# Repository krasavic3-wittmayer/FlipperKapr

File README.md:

# Flipper Kapr 🐟

Flipper Kapr is a **DIY Arduino-based experimental device**, inspired by tools like Flipper Zero.  
Its purpose is **learning, experimentation, and exploration of embedded systems and communication protocols**, not hacking or illegal activity.

This project is mainly educational and was built to understand how different modules and signals work together on microcontrollers.

## What is this?

Flipper Kapr is a personal Arduino project that combines multiple modules into a single device for:

- experimenting with signals and protocols  
- learning how hardware modules communicate  
- understanding embedded programming in practice  

It is **not** a “one-click hack tool” and does **not** magically break secure systems.

## Features

Depending on the build/version, Flipper Kapr may include:

- Infrared (IR) signal sending and receiving  
- NFC / RFID experiments  
- Simple UI (buttons, LEDs, display – if connected)  

Features depend on the hardware you attach.

## Hardware

Typical components used:

### Arduino Mega 2560

- IR transmitter / receiver  
- RFID module (e.g. 13.56 MHz / 125 kHz)  
- **Bad USB** (emulates a keyboard and sends keystrokes when connected to a computer)  

Exact wiring and modules may vary.

## Software

### Arduino (C/C++)

- Uses standard Arduino libraries and module-specific libraries  
- Code is kept simple and readable for learning purposes  

## How to use

1. Connect the hardware modules according to your setup  
2. Open the project in the Arduino IDE  
3. Select the correct board and port  
4. Upload the code  
5. Experiment responsibly  

## Legal & Ethical Notice

Flipper Kapr is intended **only for educational and experimental use**.  
You are responsible for how you use this project and any connected hardware.  
Do not use it to interfere with systems you do not own or have permission to test.

## License

This project is licensed under the **MIT License**.  
You are free to use, modify, and share it, **without any warranty**.

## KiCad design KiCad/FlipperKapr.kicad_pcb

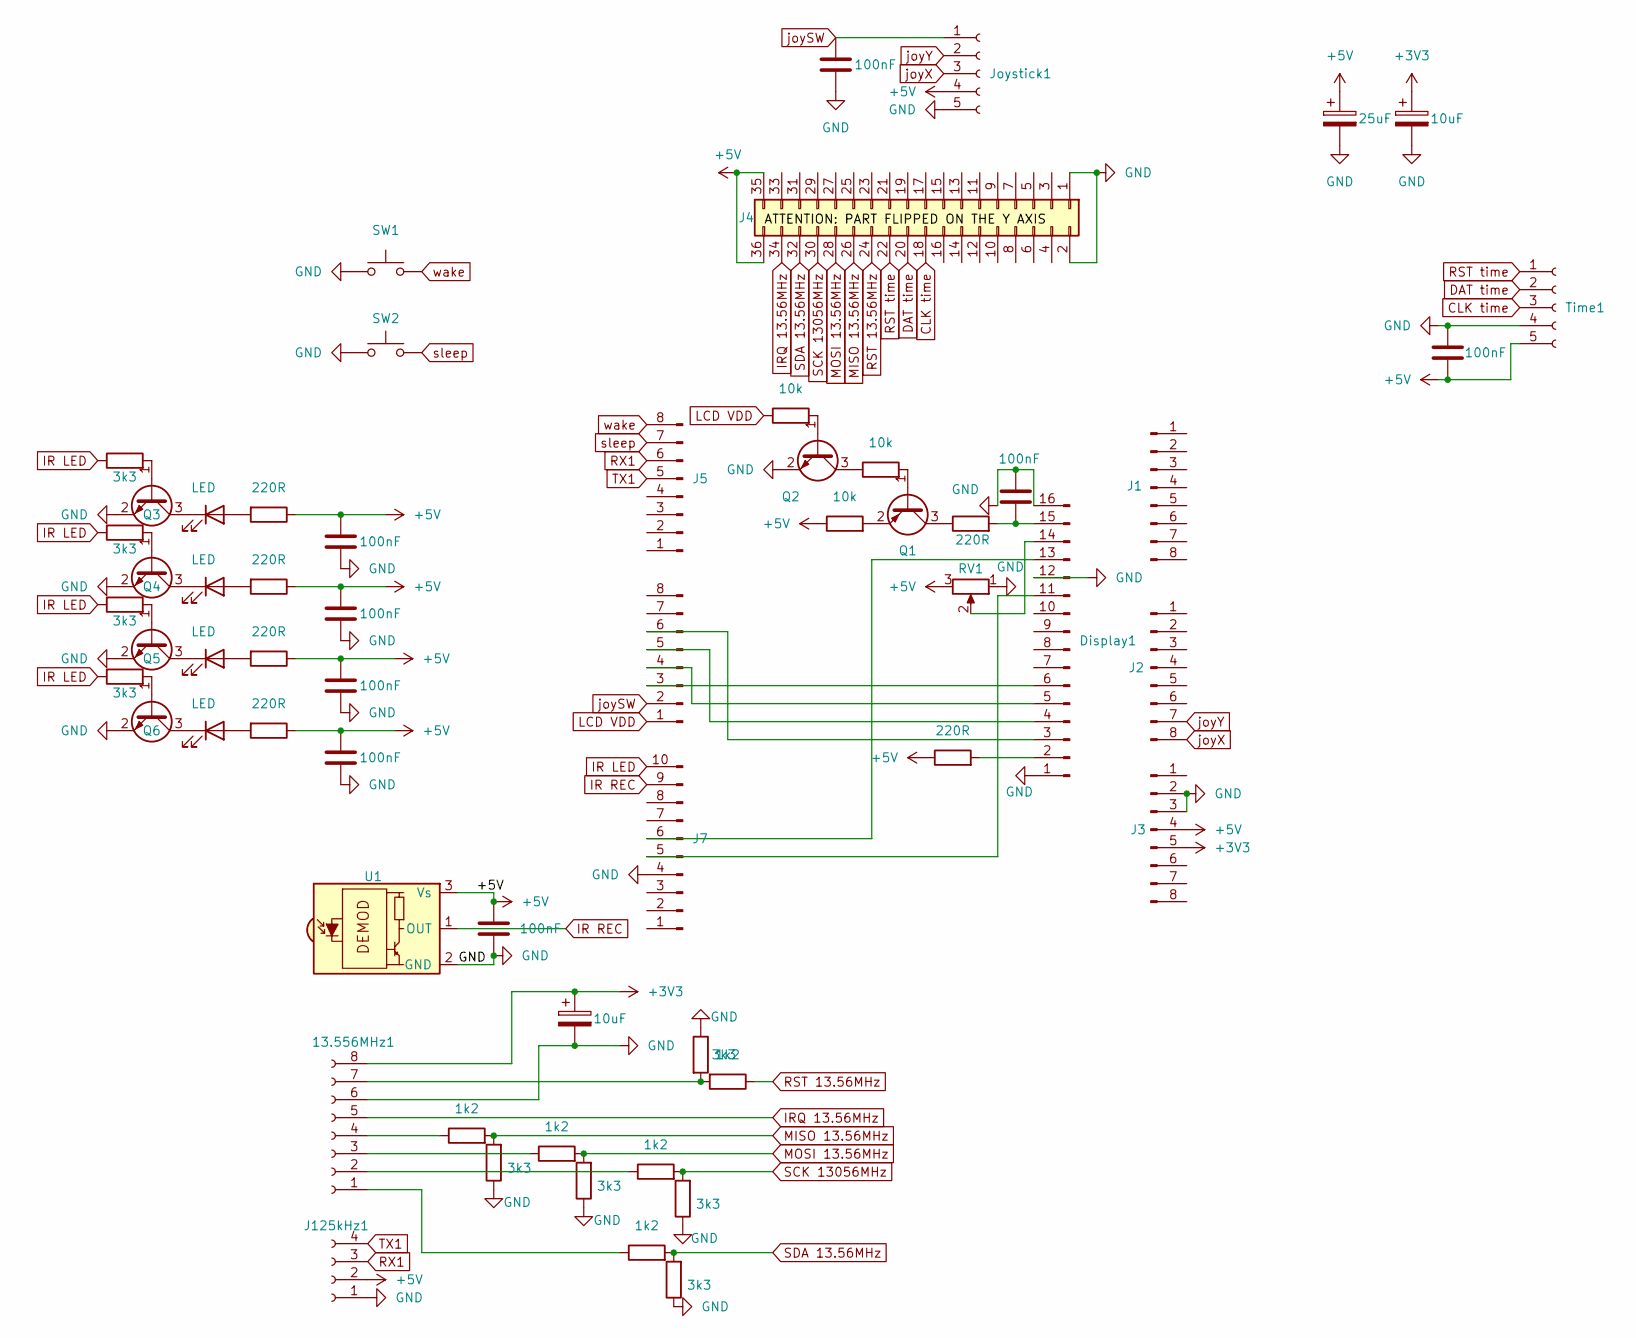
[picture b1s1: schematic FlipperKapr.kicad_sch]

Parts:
13.556MHz1: Conn_01x08_Socket; PinSocket_1x08_P2.54mm_Vertical
C1, C2, C5, C7, C8, C9, C10, C11: 100nF; C_0805_2012Metric
C3: 25uF; C_1206_3216Metric
C4, C6: 10uF; C_1206_3216Metric
D1, D2, D3, D4: LED; LED_1206_3216Metric
Display1: Conn_01x16_Pin; PinSocket_1x18_P2.54mm_Vertical
J1, J2, J3, J5, J6: Conn_01x08_Pin; PinHeader_1x08_P2.54mm_Vertical
J4: Conn_02x18_Odd_Even; PinHeader_2x18_P2.54mm_Vertical
J7: Conn_01x10_Pin; PinHeader_1x10_P2.54mm_Vertical
J125kHz1: Conn_01x04_Socket; PinSocket_1x04_P2.54mm_Vertical
Joystick1: Conn_01x05_Socket; PinSocket_1x05_P2.54mm_Vertical
Q1: SS8550; SOT-23
Q2, Q3, Q4, Q5, Q6: SS8050; SOT-23
R1, R4: 220R; R_0805_2012Metric
R2, R3, R5: 10k; R_0805_2012Metric
R6, R7, R8, R9: 220R; R_1206_3216Metric
R10, R11, R12, R13, R15, R17, R19, R21, R23: 3k3; R_0805_2012Metric
R14, R16, R18, R20, R22: 1k2; R_0805_2012Metric
RV1: R_Potentiometer; Potentiometer_Bourns_3314G_Vertical
SW1, SW2: SW_Push; SW_PUSH-12mm_Wuerth-430476085716
Time1: Conn_01x05_Socket; PinSocket_1x05_P2.54mm_Vertical
U1: TSDP341xx; Vishay_MOLD-3Pin

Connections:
+3V3: 13.556MHz1.8, C4.1, C6.1, J3.5
+5V: C2.1, C3.1, C7.1, C8.1, C9.1, C10.1, C11.2, J3.4, J4.35, J4.36, J125kHz1.2, Joystick1.4, R4.1, R5.1, R6.1, R7.1, R8.1, R9.1, RV1.3, Time1.5, U1.3 (Vs)
CLK time: J4.18, Time1.3
DAT time: J4.20, Time1.2
GND: 13.556MHz1.6, C1.1, C2.2, C3.2, C4.2, C5.2, C6.2, C7.2, C8.2, C9.2, C10.2, C11.1, Display1.1, Display1.12, Display1.16, J3.2, J3.3, J4.1, J4.2, J7.4, J125kHz1.1, Joystick1.5, Q2.2 (E), Q3.2 (E), Q4.2 (E), Q5.2 (E), Q6.2 (E), R15.1, R17.1, R19.1, R21.1, R23.1, RV1.1, SW1.1, SW2.1, Time1.4, U1.2 (GND)
IR LED: J7.10, R10.1, R11.1, R12.1, R13.1
IR REC: J7.9, U1.1 (OUT)
IRQ 13.56MHz: 13.556MHz1.5, J4.34
LCD VDD: J6.1, R3.1
MISO 13.56MHz: J4.26, R20.2, R21.2
MOSI 13.56MHz: J4.28, R18.2, R19.2
unnamed: 13.556MHz1.1, R14.1
unnamed: 13.556MHz1.2, R16.1
unnamed: 13.556MHz1.3, R18.1
unnamed: 13.556MHz1.4, R20.1
unnamed: 13.556MHz1.7, R22.2, R23.2
unnamed: D1.2 (A), R6.2
unnamed: D1.1 (K), Q3.3 (C)
unnamed: D2.2 (A), R7.2
unnamed: D2.1 (K), Q4.3 (C)
unnamed: D3.2 (A), R8.2
unnamed: D3.1 (K), Q5.3 (C)
unnamed: D4.2 (A), R9.2
unnamed: D4.1 (K), Q6.3 (C)
unnamed: Display1.2, R4.2
unnamed: Display1.3, J6.6
unnamed: Display1.4, J6.5
unnamed: Display1.5, J6.4
unnamed: Display1.6, J6.3
unnamed: Display1.11, J7.5
unnamed: Display1.13, J7.6
unnamed: Display1.14, RV1.2
unnamed: C1.2, Display1.15, R1.2
unnamed: Q1.1 (B), R2.2
unnamed: Q1.3 (C), R1.1
unnamed: Q1.2 (E), R5.2
unnamed: Q2.1 (B), R3.2
unnamed: Q2.3 (C), R2.1
unnamed: Q3.1 (B), R10.2
unnamed: Q4.1 (B), R11.2
unnamed: Q5.1 (B), R12.2
unnamed: Q6.1 (B), R13.2
RST 13.56MHz: J4.24, R22.1
RST time: J4.22, Time1.1
RX1: J5.6, J125kHz1.3
SCK 13056MHz: J4.30, R16.2, R17.2
SDA 13.56MHz: J4.32, R14.2, R15.2
TX1: J5.5, J125kHz1.4
joySW: C5.1, J6.2, Joystick1.1
joyX: J2.8, Joystick1.3
joyY: J2.7, Joystick1.2
sleep: J5.7, SW2.2
wake: J5.8, SW1.2

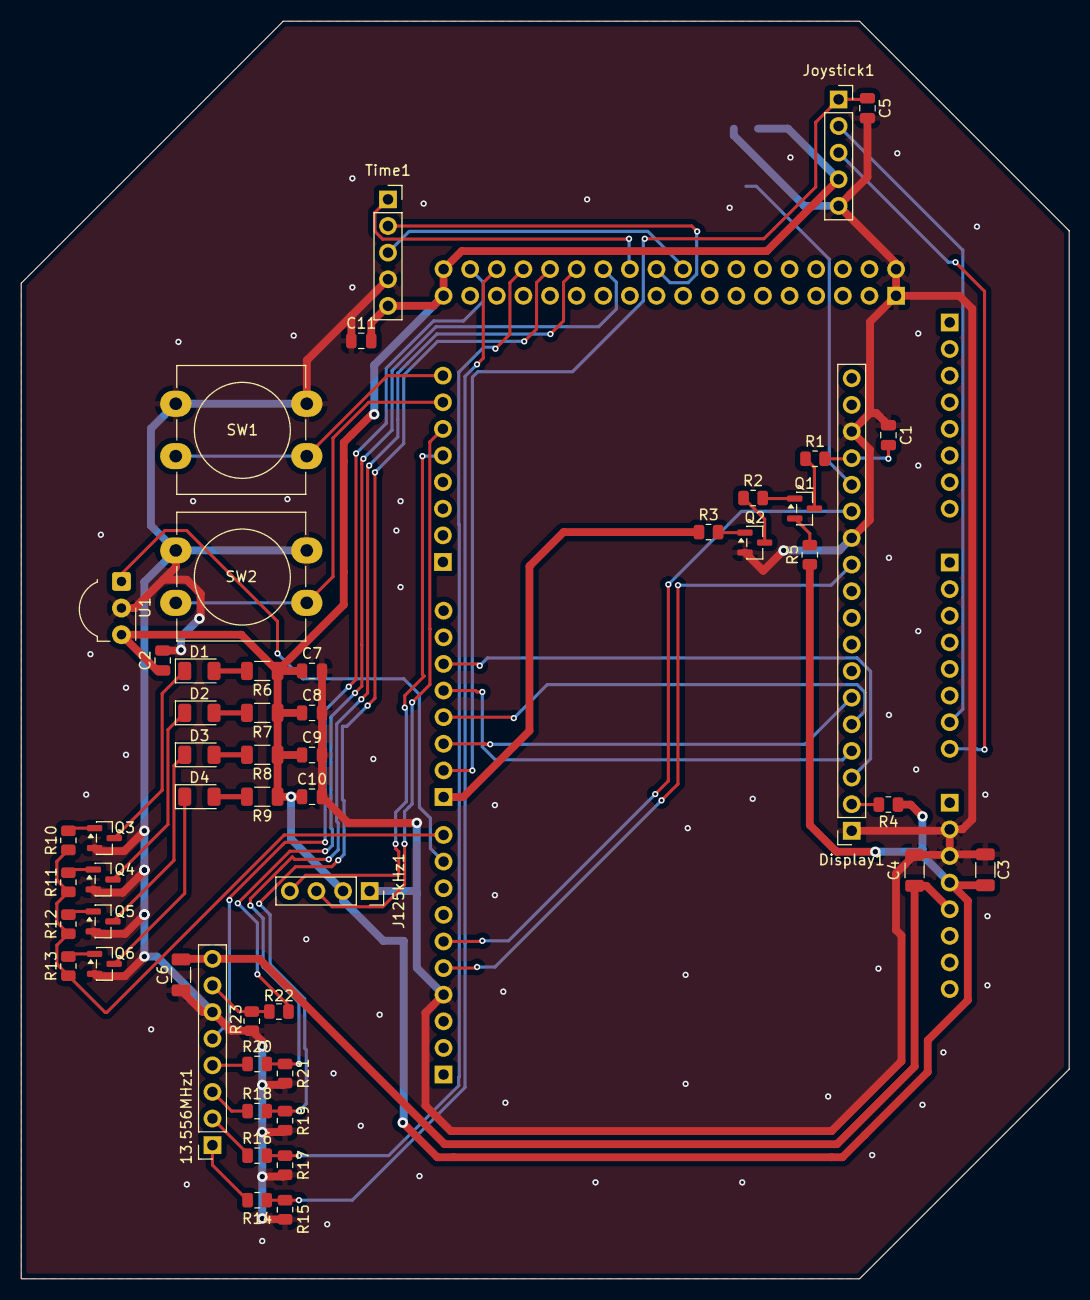
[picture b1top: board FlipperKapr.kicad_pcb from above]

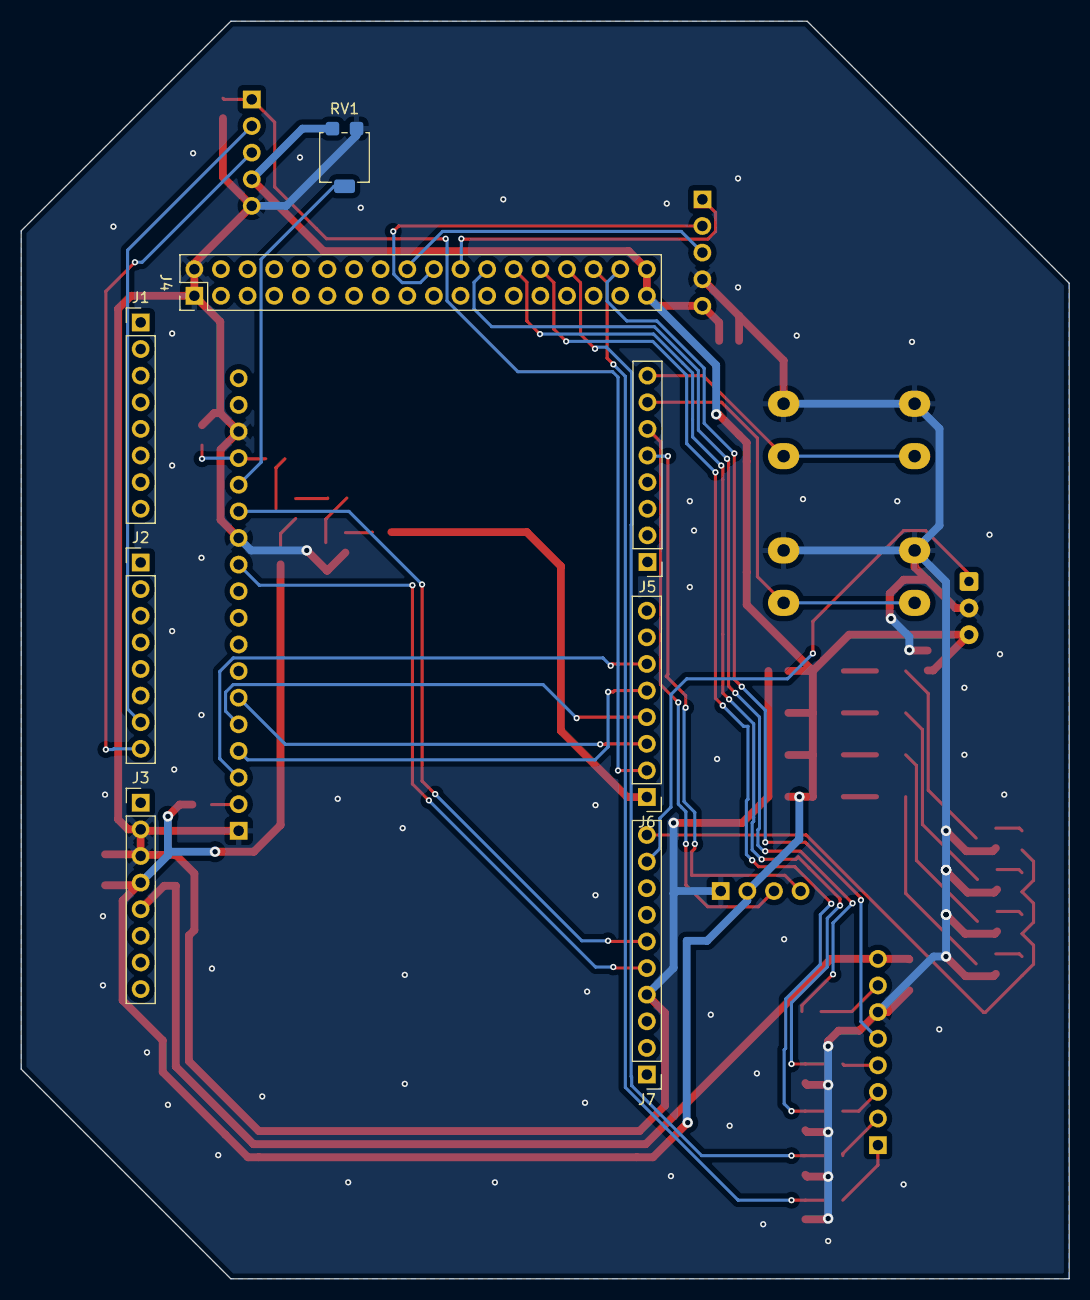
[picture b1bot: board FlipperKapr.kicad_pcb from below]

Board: 2 copper layers, 100.0 x 120.0 mm, 60 parts (8 on the bottom side), 53 nets.

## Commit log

2026-01-12 Added the main menu and the menu files
2026-01-12 Added MIT License to the project
2026-01-12 Reame has more emoji
2026-01-12 Initialized README.md with project details
    Added detailed project description, features, hardware, software, usage instructions, and legal notice.
2026-01-12 Revise README.md for improved readability
    Updated formatting and structure of README.md for clarity and emphasis.
2026-01-12 Added a schematic to work wirh
2026-01-12 Update README to remove Sub-GHz RF communication
    Removed Sub-GHz RF communication mention from features.
2026-01-12 added the rest of the menus
2026-01-13 added the bad USB menu
2026-01-13 Prove of concept about using recursive function for menus
2026-01-13 Added the KiCad project, schematic and PCB files
2026-01-13 Removed the schematic pdf for readability purposes
2026-01-13 Add LCD initialization and display function for menu options
2026-01-13 Added the python interpretation of the screen logic
2026-01-14 Added base infrastructure for menu system
2026-01-14 Added whole code for menu from prototype
2026-01-14 c++ cide fix via chatgpt to match python prototype
2026-01-14 Added back the missing includes
2026-01-14 Added back things for display chars
2026-01-14 Removed the entire code for testing purposes
2026-01-14 Added the initial functions
2026-01-14 Added the LCD ztesting
2026-01-14 Added the LCD testing
2026-01-14 Added the arduino header file
2026-01-14 Finished the LCD testing (i think the display died)
2026-01-15 testing branch for compiling cpp
2026-01-15 Fixed pin issue
2026-01-15 Make testek identical to main
2026-01-15 Deleted all the files for testing purposes
2026-01-15 Testing the RC522 module
2026-01-15 Rewrote menu function to not be based of ai code
2026-01-15 Added things to gitignore
2026-01-15 Updated main.cpp
2026-01-15 Cleaning part 1
2026-01-15 Cleaning part 2
2026-01-15 Tried to fix the RC522 module
2026-01-15 Fixed the entire main.cpp
2026-01-15 Fixed some bugs
2026-01-16 Added master save
2026-01-16 Fixed merge issue
2026-01-17 Tried setup with 2D menues
2026-01-18 Added delay
2026-01-18 Inverted side movement
2026-01-18 trying to make the namespace a header file
2026-01-18 Brought it down from 65 errors to just 4
2026-01-18 Fixed all errors
2026-01-18 Added the missing menu items
2026-01-18 Fixed the input menu lenghts
2026-01-18 Fixed the length error
2026-01-18 Changed header files
2026-01-18 Renamed the header files to cpp header files
2026-01-25 Hopefully fixes some isues
2026-01-28 Put InputMenus into seperet file, maybe fixed multi page menu problems
2026-01-28 Fixed arrow isue
2026-01-28 Lengthended the delays so it is easyer to read what is happening
2026-01-28 Tested fix for pages
2026-01-28 Tryied another fix
2026-01-28 Cleand up files
2026-01-30 Moved code to different files
2026-01-30 Made unified naming scheme
2026-02-04 Rewrote custom spedd system
2026-02-04 Added delay and lcd.clear to prevent it from bugging
2026-02-04 Added dynamic menues
2026-02-09 Added funcions for Michal
2026-02-25 Added MR522 reading
